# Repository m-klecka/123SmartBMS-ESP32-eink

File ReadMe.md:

# NOT FINISHED

## About

You have built your own battery pack with the awesome [123 Smart BMS]?
You want to control something based on the BMS data?
Or maybe you want to share this data via WiFi and an ESP32?
Maybe upload it somewhere for monitoring?
Then this code may help you to do just that.

## How it Works

On each battery pack you will have at least one `begin` and one `end` module of the [123 Smart BMS].
Also, there can be many so called `between` modules.
These modules are connected in series via two wires which are used as a communication channel between the modules.
See [manual] for details.

In fact these modules use a (one way) serial/UART connection to send data from the `begin` to the `end` module.
Each `between` modules can then add/modify data and send the data packet to the next module until the `end` module is reached.
The packet size is fixed to 58 bytes and only one of the between modules will add cell specific data per cycle.
Data related to the pack in general is sent each cycle.
The `end` module has a free connector which can be used to grab these packets.
Here is what I found by reverse engineering a bit.
But no guarantee😋.

- Pin 1: (inverted) data
- Pin 2: ground/negative of the cell the module is mounted on
- Interface: UART
- Baud rate: 9600
- Voltage: depends on cell voltage, usually 2.5V to 3.65V for LiFePo4
- 58 bytes of data per packet

## Connect it to Arduino

### Wait a Second

Before burning your house down by messing around with the great [123 Smart BMS], please check out their official [123 Smart BMS USB Cable].
It allows you to safely connect the BMS to basically any computer.
It provides important safety features like galvanic isolation and they even created a [Venus OS Integration].
Awesome!
If you still want to DIY it, then feel free to proceed.

### Inverted and Isolated by Hardware (Recommended)

> :information_source: This setup is the safest way of connecting your microcontroller to the BMS.
> It provides galvanic isolation and reduces the risk of shorts circuits drastically.

- Connect `BMS_DATA` to pin 1 of the BMS data port
- Connect `BMS_GROUND` to pin 2 of the BMS
- Connect `ARDUINO_VCC` to the supply voltage of your Arduino (3.3V or 5V)
- Connect `ARDUINO_DATA` to any unused pin
- Connect `ARDUINO_GND` to ground of the Arduino
- Open [main.cpp](./src/main.cpp)
  - Set `BMS_SERIAL_RX_PIN` to the used pin
  - Set `BMS_SERIAL_INVERT` to `false`

### Invert by Software and Connect Directly 🔥

> :warning: When using a direct connection, keep in mind that your microcontroller and/or PC is directly connected to a huge battery.
> It is very easy to create a short circuit that kills your microcontroller, PC, the BMS and/or even you.
> You have been warned!

- Make sure the voltage does not exceed the allowed voltage of your microcontroller
- Connect ground of your microcontroller to the negative of the battery cell with the `end` module
- Connect pin 1 of the BMS data port to any unused Arduio pin
- Open [main.cpp](./src/main.cpp)
  - Set `BMS_SERIAL_RX_PIN` to the used pin
  - Set `BMS_SERIAL_INVERT` to `true`

## So whats next?

Well, upload the code and open your serial monitor.
Your Arduino should print out the battery data received from the [123 Smart BMS].
You can do with this data what every you want.
For example, turn on/off an inverter depending on the SOC.
Or upload the data to the internet with an ESP32 for monitoring.
Or...
Or...
You get it!

<!-- References -->

[123 Smart BMS]: https://123electric.eu/products/123smartbms-gen3/
[123 Smart BMS USB Cable]: https://123electric.eu/products/123smartbms-to-usb/
[Venus OS Integration]: https://github.com/123electric/123SmartBMS-Venus
[manual]: https://123electric.eu/downloads/123smartbms/123SmartBMS_gen3_manual.pdf

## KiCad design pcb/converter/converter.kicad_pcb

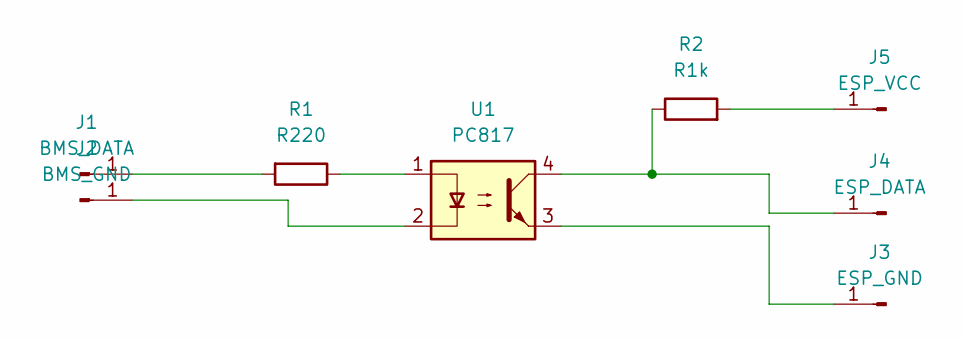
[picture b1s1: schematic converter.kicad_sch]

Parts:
J1: BMS_DATA; SolderPad5x3mm
J2: BMS_GND; SolderPad5x3mm
J3: ESP_GND; SolderPad5x3mm
J4: ESP_DATA; SolderPad5x3mm
J5: ESP_VCC; SolderPad5x3mm
R1: R220; R_0805_2012Metric
R2: R1k; R_0805_2012Metric
U1: PC817; DIP-4_W7.62mm_SMDSocket_SmallPads

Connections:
unnamed: J1.1, R1.2
unnamed: J2.1, U1.2
unnamed: J3.1, U1.3
unnamed: J4.1, R2.1, U1.4
unnamed: J5.1, R2.2
unnamed: R1.1, U1.1

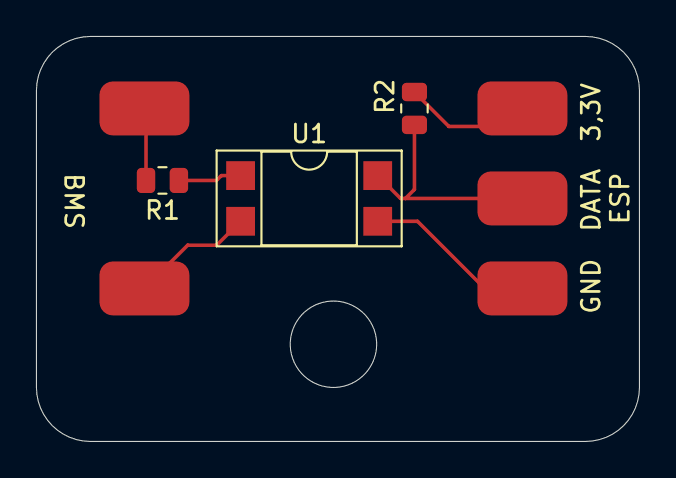
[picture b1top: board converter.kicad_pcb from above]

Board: 2 copper layers, 33.5 x 22.5 mm, 8 parts (0 on the bottom side), 6 nets.

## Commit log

2024-10-30 Added display part
2024-10-30 Edited display data
2024-11-01 Edits
2024-11-01 Edited display updates
2024-11-01 merged code from origin and edited
2024-11-01 added icons
2024-11-02 moved files
2024-11-02 fonts
2024-11-04 test icons
2024-11-04 edit messages
2024-11-05 edit
2024-11-05 added display printing
2024-11-06 Deleted unused fonts + display formating edits
2024-11-06 Deleted unused files
2024-11-08 Added pcb
2024-11-09 edited pcb
2024-11-09 edit footprints library
2024-11-09 gerber files
2024-11-11 edit battery icon/s
2024-11-12 icon edits
2024-11-14 edit error detection
2024-11-14 revert
2024-11-14 Revert "edit error detection"
    This reverts commit 0505418405cb5f82fdf6ef2888511a2492d51ebe.
2024-11-22 gitignore
2024-12-02 Probably final edits, added remaining charge time calculation
